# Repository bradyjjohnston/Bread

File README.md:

# 🍞 SALT - Slice And Loaf Telemetry

> A modular home automation and environmental sensing platform, developed in collaboration with **EE4737** and the open-source [BREAD] project.

---

## Overview

BREAD is a modular embedded systems architecture built around a central **Loaf** board and hot-swappable **Slice** modules. Each slice handles its own sensing or control functionality and communicates back to the loaf over a shared protocol (UART). Together, they form a capable at-home weather station and automation hub.

---

## Architecture

```
┌────────────────────────────────────────┐
│              Loaf (Main Board)         │
│   Central controller with female conn. │
│   handles aggregation, display, logic  │
└────────┬────────┬────────┬─────────────┘
         │        │        │
    ┌────┴──┐ ┌───┴──┐ ┌───┴──┐
    │Slice 1│ │Slice2│ │Slice3│  ...
    │SENSE  │ │ ACT. │ │ OPT. │
    └───────┘ └──────┘ └──────┘
```

- **Loaf** — the main board with female connectors, acts as the central hub
- **Slices** — individual modules that plug into the loaf via edge connectors and expose sensor data or control outputs over UART/I2C

---

## Features

- 🌡️ **Environmental monitoring** — temperature, humidity, pressure (BME280)
- 🌐 **Weather data integration** — pulls external weather API data
- 📡 **Modular slice communication** — UART packet protocol between slices and loaf
- 🔌 **Plug-and-play expansion** — add new slices without redesigning the core system
- 🏠 **Home automation ready** — designed to grow into broader automation use cases

---

## Hardware

| Component | Role |
|-----------|------|
| LOAF | Sensor slice microcontroller |
| Sense Slice | temp / humidity / pressure sensor / boot sensor |
| Actuation Slice | salt distribution motor control |
| Optics Slice | camera processing and control |
| Power Slice | power outage detection and power distribution |

---

## Communication Protocol

Slices send formatted UART packets to the loaf via DMA when requested by the master MCU. Each packet includes:

- Formatted sensor data

---

## Getting Started

> ⚠️ Hardware required. Software setup instructions coming soon.

1. Clone this repo
2. Open in **STM32CubeIDE**
3. Flash the slice firmware to your Nucleo F303K8
4. Connect the slice to the loaf board via the edge connector
5. Monitor output over UART at `115200` baud

---

## Project Context

This system was developed as part of **EE4737** coursework and builds on the open-source BREAD framework. The goal is a practical, extensible platform for real-world embedded sensing and home automation experimentation.

---

## License

MIT — see `LICENSE` for details.

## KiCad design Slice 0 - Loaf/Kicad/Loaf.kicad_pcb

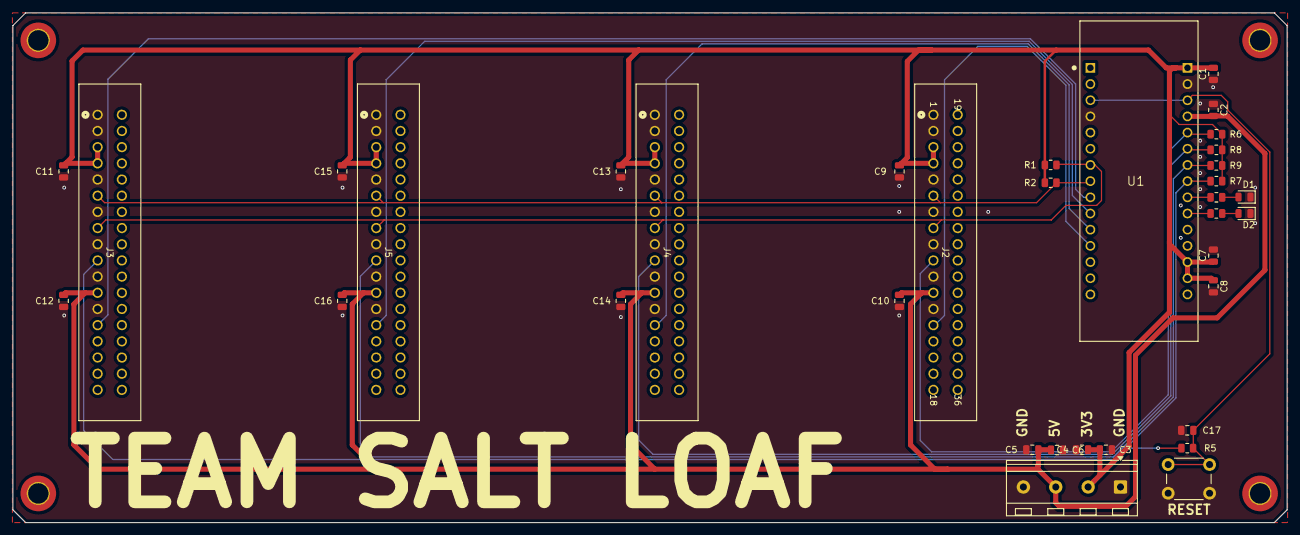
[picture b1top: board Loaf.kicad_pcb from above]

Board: 2 copper layers, 200.0 x 80.0 mm, 35 parts (0 on the bottom side), 18 nets.

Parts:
C1, C2, C7, C8, C17: 0.1uF; C_0805_2012Metric
C3, C4, C5, C6, C9, C10, C11, C12, C13, C14, C15, C16: 10uF; C_0805_2012Metric
D1: USER LED1; LED_0805_2012Metric
D2: USER LED2; LED_0805_2012Metric
J1: Power Input Terminal; TerminalBlock_RND_205-00234_1x04_P5.08mm_Horizontal
J2, J3, J4, J5: 36p Edge Connector; EdgeConnector
R1, R2, R3, R4, R5, R6, R7, R8, R9: 4.7k; R_0805_2012Metric
SW1: BOOT; SW_PUSH_6mm_H5mm
U1: NUCLEO-F303K8; MODULE_NUCLEO-F303K8

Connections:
3V3: C1.2, C3.2, C4.2, C7.1, C8.1, C9.1, C11.1, C13.1, C15.1, J1.2, J2.3, J2.4, J3.3, J3.4, J4.3, J4.4, J5.3, J5.4, R1.2, R2.2, R5.2, R6.1, R7.1, R8.1, R9.1, U1.16 (VIN), U1.28 (AREF), U1.29 (3V3)
5V: C2.2, C5.1, C6.1, C10.1, C12.1, C14.1, C16.1, J1.3, J2.12, J3.12, J4.12, J5.12, U1.19 (5V)
DET_ACT: J5.10, R9.2, U1.22 (A6)
DET_OPT: J3.10, R7.2, U1.23 (A5)
DET_POW: J4.10, R8.2, U1.21 (A7)
DET_SENSE: J2.10, R6.2, U1.20 (A2)
EXT1_ACT: J5.14, U1.10 (F0)
EXT1_OPT: J3.14, U1.9 (B1)
EXT1_POW: J4.14, U1.11 (F1)
EXT1_SENSE: J2.14, U1.12 (A8)
GND: C1.1, C2.1, C3.1, C4.1, C5.2, C6.2, C7.2, C8.2, C9.2, C10.2, C11.2, C12.2, C13.2, C14.2, C15.2, C16.2, C17.2, D1.1 (K), D2.1 (K), J1.1, J1.4, J2.1, J2.2, J2.5, J2.7, J2.9, J2.11, J2.13, J3.1, J3.2, J3.5, J3.7, J3.9, J3.11, J3.13, J4.1, J4.2, J4.5, J4.7, J4.9, J4.11, J4.13, J5.1, J5.2, J5.5, J5.7, J5.9, J5.11, J5.13, SW1.1, U1.4 (GND), U1.17 (GND)
I2C_SCL: J2.6, J3.6, J4.6, J5.6, R2.1, U1.8 (B6)
I2C_SDA: J2.8, J3.8, J4.8, J5.8, R1.1, U1.7 (B7)
NRST: C17.1, R5.1, SW1.2, U1.3 (NRST), U1.18 (NRST)
unnamed: D1.2 (A), R4.2
unnamed: D2.2 (A), R3.2
unnamed: R3.1, U1.25 (A3)
unnamed: R4.1, U1.24 (A4)

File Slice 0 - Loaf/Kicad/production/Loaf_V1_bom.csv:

Designator,Footprint,Quantity,Value,LCSC Part #
"C1, C17, C2, C7, C8",0805,5,0.1uF,
"C10, C11, C12, C13, C14, C15, C16, C3, C4, C5, C6, C9",0805,12,10uF,
D1,0805,1,USER LED1,
D2,0805,1,USER LED2,
J1,TerminalBlock_RND_205-00234_1x04_P5.08mm_Horizontal,1,Power Input Terminal,
"J2, J3, J4, J5",EdgeConnector,4,36p Edge Connector,
"R1, R2, R3, R4, R5, R6, R7, R8, R9",0805,9,4.7k,
SW1,SW_PUSH_6mm_H5mm,1,BOOT,
U1,MODULE_NUCLEO-F303K8,1,NUCLEO-F303K8,

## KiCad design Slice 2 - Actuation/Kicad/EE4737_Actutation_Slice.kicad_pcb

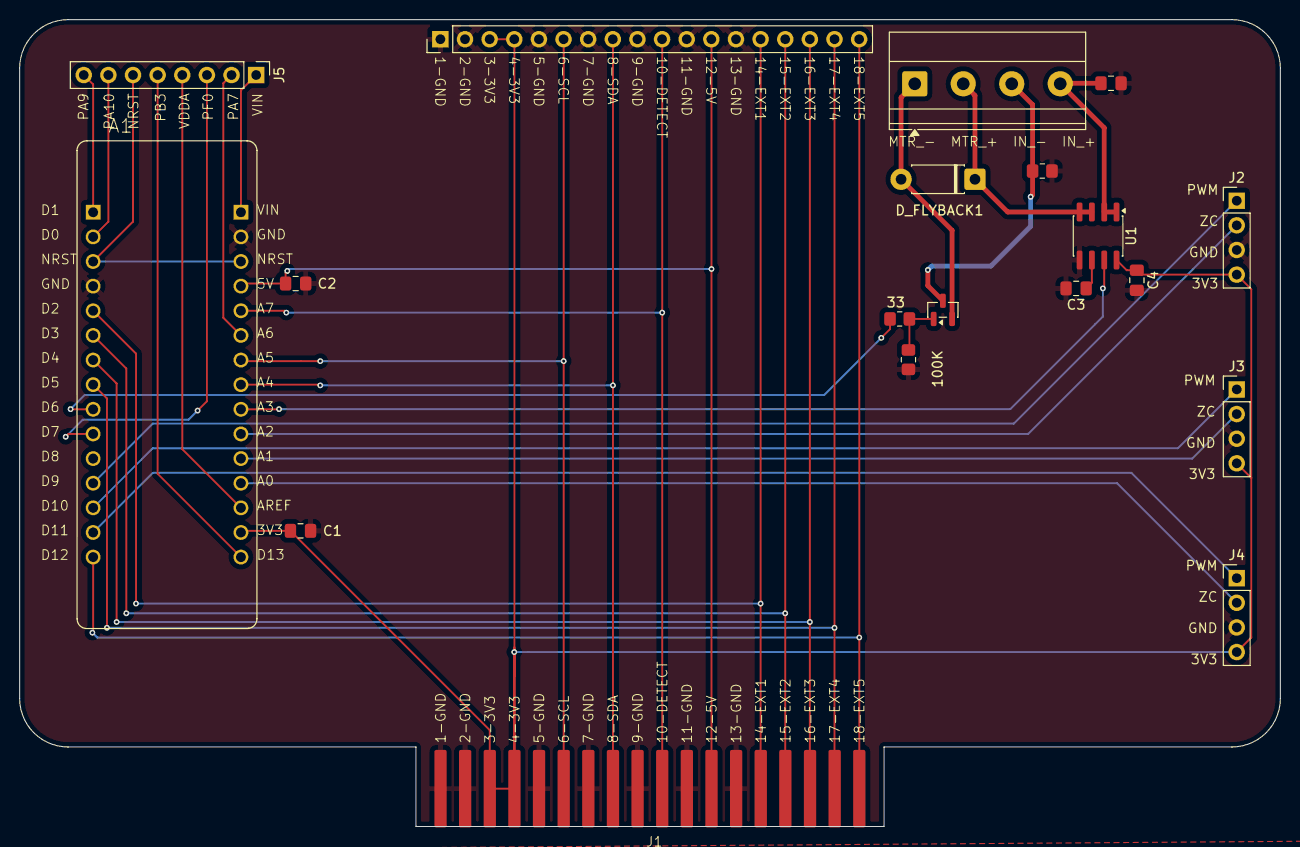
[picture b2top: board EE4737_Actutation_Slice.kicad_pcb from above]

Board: 2 copper layers, 130.0 x 83.2 mm, 18 parts (0 on the bottom side), 33 nets.

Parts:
33: 33; R_0805_2012Metric_Pad1.20x1.40mm_HandSolder
100K: 100k; R_0805_2012Metric_Pad1.20x1.40mm_HandSolder
A1: nucleo32
C1, C2: 100nF; C_0805_2012Metric_Pad1.18x1.45mm_HandSolder
C3: 1nF; C_0805_2012Metric_Pad1.18x1.45mm_HandSolder
C4: .1uF; C_0805_2012Metric_Pad1.18x1.45mm_HandSolder
C_Motor1: 100nF; C_0805_2012Metric_Pad1.18x1.45mm_HandSolder
D_FLYBACK1: D; D_DO-41_SOD81_P7.62mm_Horizontal
J1: Conn_01x18; Team Salt Slice
J2, J3, J4: Conn_01x04; PinHeader_1x04_P2.54mm_Vertical
J5: Conn_01x08; PinHeader_1x08_P2.54mm_Vertical
J_motor1: Screw_Terminal_01x04; TerminalBlock_Phoenix_MKDS-1,5-4_1x04_P5.00mm_Horizontal
Q_Motor1: Q_NMOS_GDS; SOT-23
R_MPD2: 0; R_0805_2012Metric_Pad1.20x1.40mm_HandSolder
U1: ACS725xLCTR-50AB; SOIC-8_3.9x4.9mm_P1.27mm

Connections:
3V3: A1.4.14 (VDD), C1.1, C4.1, J1.3, J1.4, J2.4, J3.4, J4.4, U1.8 (VCC)
5V: A1.4.4 (5V), C2.1, J1.12
CS+19V5: C_Motor1.1, J_motor1.4, U1.1 (IP+), U1.2 (IP+)
CS-19V5: D_FLYBACK1.1 (K), J_motor1.2, U1.3 (IP-), U1.4 (IP-)
DETECT: A1.4.5 (PA2), J1.10
EXT1: A1.3.5 (PA12), J1.14
EXT2: A1.3.6 (PB0), J1.15
EXT3: A1.3.7 (PB7), J1.16
EXT4: A1.3.8 (PB6), J1.17
EXT5: A1.3.15 (PB4), J1.18
EXT_19V5_-: J_motor1.3, Q_Motor1.3 (S), R_MPD2.1
GND: 100K.2, A1.3.4 (GND), A1.4.2 (GND), C1.2, C2.2, C3.2, C4.2, C_Motor1.2, J1.1, J1.2, J1.5, J1.7, J1.9, J1.11, J1.13, J2.3, J3.3, J4.3, R_MPD2.2, U1.5 (GND)
MTR_-: D_FLYBACK1.2 (A), J_motor1.1, Q_Motor1.2 (D)
MotorPWM: 33.1, A1.3.9 (PB1)
NRST: A1.3.3 (NRST), A1.4.3 (NRST), J5.6
unnamed: 33.2, 100K.1, Q_Motor1.1 (G)
unnamed: C3.1, U1.6 (FILTER)
PA4: A1.4.9 (PA4), U1.7 (VIOUT)
PA7: A1.4.6 (PA7), J5.2
PA9: A1.3.1 (PA9), J5.8
PA10: A1.3.2 (PA10), J5.7
PB3: A1.4.15 (PB3), J5.5
PF0: A1.3.10 (PF0), J5.3
PWM_1: A1.3.12 (PA8), J2.1
PWM_2: A1.3.13 (PA11), J3.1
PWM_3: A1.3.14 (PB5), J4.1
SCL: A1.4.7 (PA6), J1.6
SDA: A1.4.8 (PA5), J1.8
VDDA: A1.4.13 (VDDA), J5.4
VIN: A1.4.1 (VIN), J5.1
ZC_1: A1.4.10 (PA3), J2.2
ZC_2: A1.4.11 (PA1), J3.2
ZC_3: A1.4.12 (PA0), J4.2

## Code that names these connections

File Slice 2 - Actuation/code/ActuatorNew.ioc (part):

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Mcu.Name=STM32F303K(6-8)Tx
Mcu.Package=LQFP32
Mcu.UserName=STM32F303K8Tx
PA0.GPIOParameters=GPIO_PuPd
PA0.GPIO_PuPd=GPIO_NOPULL
PA0.Signal=GPXTI0
PA1.GPIOParameters=GPIO_PuPd
PA1.GPIO_PuPd=GPIO_NOPULL
PA1.Signal=GPXTI1
PA11.Signal=GPIO_Output
PA13.GPIOParameters=GPIO_Label
PA13.GPIO_Label=SWDIO
PA13.Mode=Serial_Wire
PA13.Signal=SYS_JTMS-SWDIO
PA14.GPIOParameters=GPIO_Label
PA14.GPIO_Label=SWCLK
PA14.Mode=Serial_Wire
PA14.Signal=SYS_JTCK-SWCLK
PA15.GPIOParameters=GPIO_Label
PA15.GPIO_Label=VCP_RX
PA15.Signal=USART2_RX
PA2.Signal=GPIO_Output
PA3.GPIOParameters=GPIO_PuPd
PA3.GPIO_PuPd=GPIO_NOPULL
PA3.Signal=GPXTI3
PA4.Signal=SharedAnalog_PA4
PA8.Signal=S_TIM1_CH1
PB1.Signal=GPIO_Output
PB5.Signal=GPIO_Output
PB6.Mode=Asynchronous
PB6.Signal=USART1_TX
PB7.Mode=Asynchronous
PB7.Signal=USART1_RX
PF0\ /\ OSC_IN.GPIOParameters=GPIO_Label
PF0\ /\ OSC_IN.GPIO_Label=MCO
PF0\ /\ OSC_IN.Mode=HSE-External-Clock-Source
PF0\ /\ OSC_IN.Signal=RCC_OSC_IN
RCC.HSEPLLFreq_Value=8000000
RCC.HSE_VALUE=8000000
RCC.SYSCLKFreq_VALUE=8000000
board=NUCLEO-F303K8
boardIOC=true

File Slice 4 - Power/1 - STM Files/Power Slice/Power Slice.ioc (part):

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Mcu.Name=STM32F303K(6-8)Tx
Mcu.Package=LQFP32
Mcu.UserName=STM32F303K8Tx
PA0.Signal=SharedAnalog_PA0
PA1.Signal=SharedAnalog_PA1
PA13.GPIOParameters=GPIO_Label
PA13.GPIO_Label=SWDIO
PA13.Signal=SYS_JTMS-SWDIO
PA14.GPIOParameters=GPIO_Label
PA14.GPIO_Label=SWCLK
PA14.Signal=SYS_JTCK-SWCLK
PA15.GPIOParameters=GPIO_Label
PA15.GPIO_Label=VCP_RX
PA15.Signal=USART2_RX
PA2.Signal=SharedAnalog_PA2
PA3.Signal=ADC1_IN4
PA4.Signal=GPIO_Output
PB0.Signal=GPIO_Output
PB3.GPIOParameters=GPIO_PuPd
PB3.GPIO_PuPd=GPIO_PULLUP
PB3.Mode=Full_Duplex_Master
PB3.Signal=SPI1_SCK
PB4.GPIOParameters=GPIO_PuPd
PB4.GPIO_PuPd=GPIO_PULLUP
PB4.Mode=Full_Duplex_Master
PB4.Signal=SPI1_MISO
PB5.GPIOParameters=GPIO_PuPd
PB5.GPIO_PuPd=GPIO_PULLUP
PB5.Mode=Full_Duplex_Master
PB5.Signal=SPI1_MOSI
PB6.Mode=Asynchronous
PB6.Signal=USART1_TX
PB7.Mode=Asynchronous
PB7.Signal=USART1_RX
PF0\ /\ OSC_IN.Signal=GPIO_Output
PF1\ /\ OSC_OUT.Signal=GPIO_Output
RCC.HSEPLLFreq_Value=8000000
RCC.HSE_VALUE=8000000
RCC.SYSCLKFreq_VALUE=8000000
board=NUCLEO-F303K8
boardIOC=true

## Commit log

2026-04-22 Updated Files
